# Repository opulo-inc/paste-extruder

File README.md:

# LumenPnP Paste Extruder

This repository contains the source for the paste extruder toolhead for the LumenPnP.

This extruder head is designed for solder paste dispensing applications. It replaces the right toolhead on any version LumenPnP.
Controlling this toolhead is currently done using [paste.opulo.io](https://paste.opulo.io), a web-based utility for automatically dispensing solder paste onto PCB pads based on your gerber files.

The source CAD for the extruder was originally designed as a replacement left nozzle. However, the toolhead works much better when replacing the right nozzle. 

## Help

Feel free to hop in the [LumenPnP Discord Server](https://discordapp.com/invite/TCwy6De ) to help debug and troubleshoot using the extruder head. Also, please feel free to add Github Issues on this repository if you discover any problems.

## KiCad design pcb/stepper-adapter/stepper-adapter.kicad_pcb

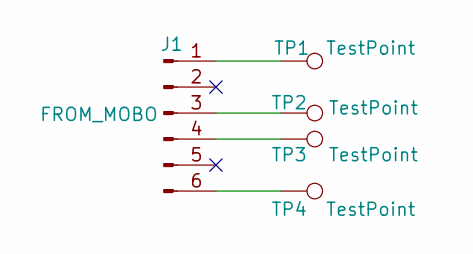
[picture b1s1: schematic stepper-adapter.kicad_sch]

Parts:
J1: FROM_MOBO; Molex_Micro-Latch_53254-0670_1x06_P2.00mm_Horizontal
TP1, TP2, TP3, TP4: TestPoint; TestPoint_Keystone_5015_Micro-Minature

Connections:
unnamed: J1.1, TP1.1
unnamed: J1.3, TP2.1
unnamed: J1.4, TP3.1
unnamed: J1.6, TP4.1

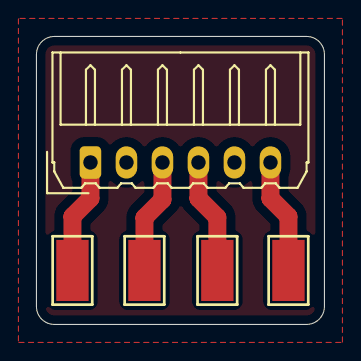
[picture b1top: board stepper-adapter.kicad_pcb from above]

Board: 2 copper layers, 16.0 x 16.0 mm, 5 parts (0 on the bottom side), 4 nets.

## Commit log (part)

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2024-10-11 fixed bom count of m2 bolt
2024-11-03 restructuring plus github ci test for autobom
2024-11-03 removes autobom version
2024-11-03 switching back
2024-11-03 sets specific version
2024-11-03 adds other run methods
2024-11-15 bulk commit with paste support
2024-11-16 clarifies the mirror flip in readme
2024-11-16 adds wip for vid
2024-11-16 atm machine is redundant
2024-12-03 adds instructions docs
2025-01-29 Removes .FCStd1 from repo
2025-01-31 loosens extruder-gear shaft fit
